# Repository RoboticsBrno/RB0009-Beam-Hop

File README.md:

Beambot module that *hops* the motor when the capacitor is charged enough.

Taken from https://www.instructables.com/Tiny-Solar-Powered-Light-Seeking-BEAM-Bot-Mini-Pho/

Two instances are typically required for one bot.

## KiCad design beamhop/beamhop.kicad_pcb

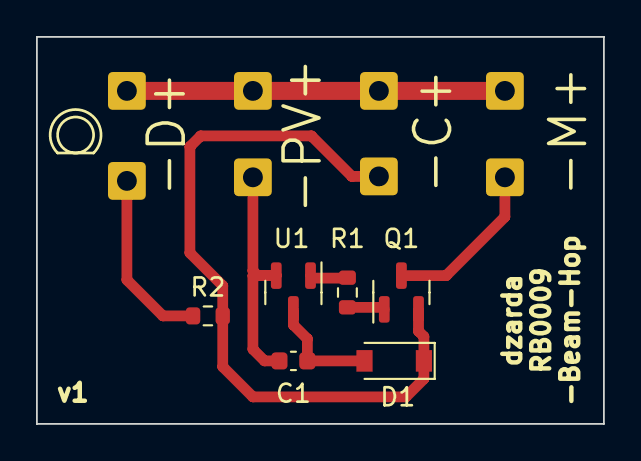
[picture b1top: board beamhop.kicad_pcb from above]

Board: 2 copper layers, 31.5 x 21.5 mm, 14 parts (0 on the bottom side), 8 nets.

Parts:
C1: 470p; C_0603_1608Metric
D1: 1N4148W; D_SOD-123
H1, H2, H3, H4, H5, H6, H7, H8: MountingHole_Pad; SolderWire-0.5sqmm_1x01_D0.9mm_OD2.1mm
Q1: BC847; SOT-23
R1, R2: 100; R_0603_1608Metric
U1: MCP101-270D; SOT-23

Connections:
GND: D1.1 (K), H2.1, Q1.2 (E), R2.2
unnamed: C1.1, D1.2 (A), U1.3 (VSS)
unnamed: C1.2, H4.1, U1.2 (VDD)
unnamed: H6.1, Q1.3 (C)
unnamed: H8.1, R2.1
unnamed: Q1.1 (B), R1.2
unnamed: R1.1, U1.1 (RST)
VCC: H1.1, H3.1, H5.1, H7.1

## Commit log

2022-05-21 Add v1
